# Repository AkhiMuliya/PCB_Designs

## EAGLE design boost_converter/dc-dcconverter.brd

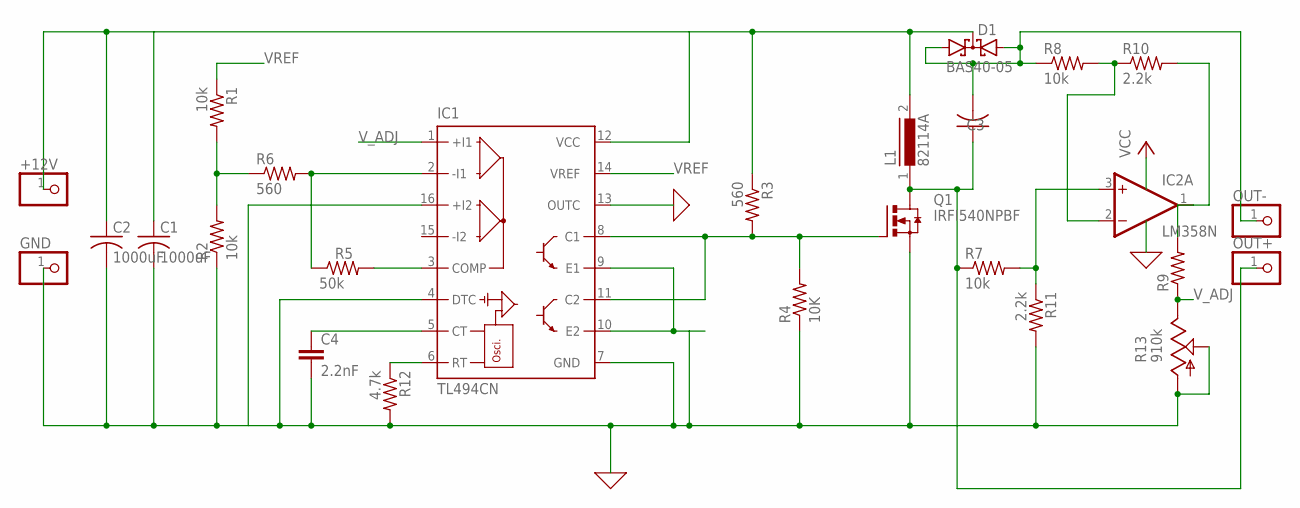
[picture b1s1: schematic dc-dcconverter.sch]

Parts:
+12V: PINHD-1X1; 1X01
C1, C2: 1000uF; C025-024X044
C3: C-US025-024X044; C025-024X044
C4: 2.2nF; C2.5-3
D1: BAS40-05; SOT23
GND: PINHD-1X1; 1X01
IC1: TL494CN; DIL16
IC2: LM358N; DIL08
L1: 82114A
OUT+: PINHD-1X1; 1X01
OUT-: PINHD-1X1; 1X01
Q1: IRFI540NPBF; TO220BH
R1, R2, R7, R8: 10k; 0204/5
R3, R6: 560; 0204/5
R4: 10K; 0204/5
R5: 50k; 0204/5
R9: R-US_0204/5; 0204/5
R10, R11: 2.2k; 0204/5
R12: 4.7k; 0204/5
R13: 910k; CA6H

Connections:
0: IC1.13 (OUTC)
GND: C1.2, C2.2, C4.2, GND.1, IC1.4 (DTC), IC1.7 (GND), IC1.9 (E1), IC1.10 (E2), IC1.16 (+I2), Q1.S, R2.1, R4.1, R11.2, R12.2, R13.A, R13.S
unnamed: IC1.2 (-I1), R5.1, R6.2
unnamed: IC1.3 (COMP), R5.2
unnamed: IC1.6 (RT), R12.1
unnamed: C4.1, IC1.5 (CT)
unnamed: IC1.8 (C1), IC1.11 (C2), Q1.G, R3.2, R4.2
unnamed: IC2.2 (-IN), R8.2, R10.1
unnamed: C3.1, L1.1, OUT+.1, Q1.D, R7.1
unnamed: C3.2, D1.1 (A1), D1.2 (A2), OUT-.1, R8.1
unnamed: IC2.1 (OUT), R9.2, R10.2
unnamed: R1.2, R2.2, R6.1
unnamed: IC2.3 (+IN), R7.2, R11.1
unnamed: +12V.1, C1.1, C2.1, D1.3 (C), IC1.12 (VCC), L1.2, R3.1
V+: IC2.8 (V+)
V-: IC2.4 (V-)
VREF: R1.1
V_ADJ: R9.1, R13.E

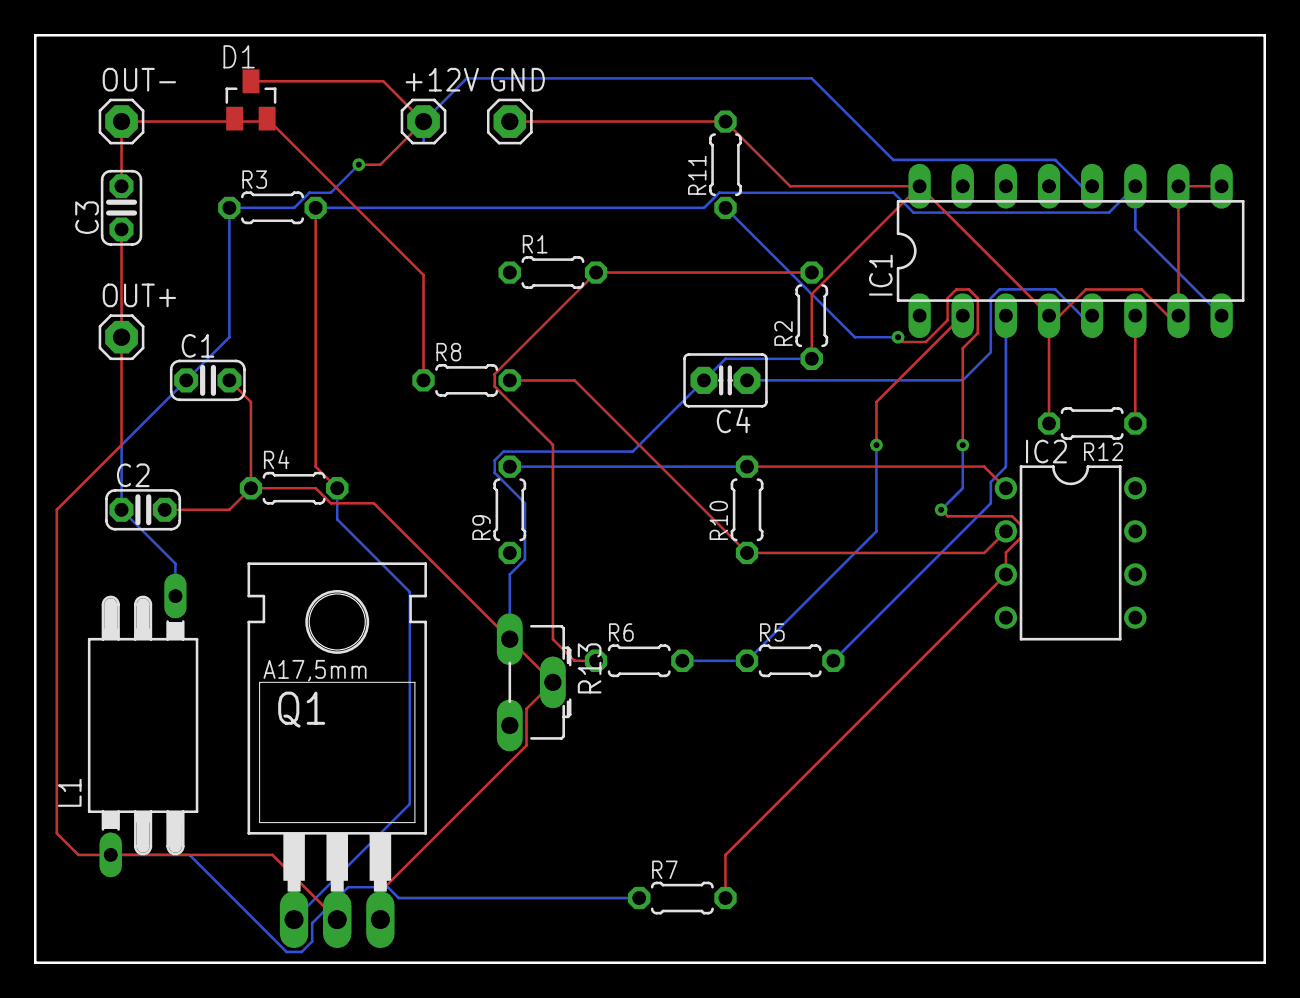
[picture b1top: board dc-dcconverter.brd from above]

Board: 2 copper layers, 72.4 x 54.6 mm, 26 parts (0 on the bottom side), 14 nets.

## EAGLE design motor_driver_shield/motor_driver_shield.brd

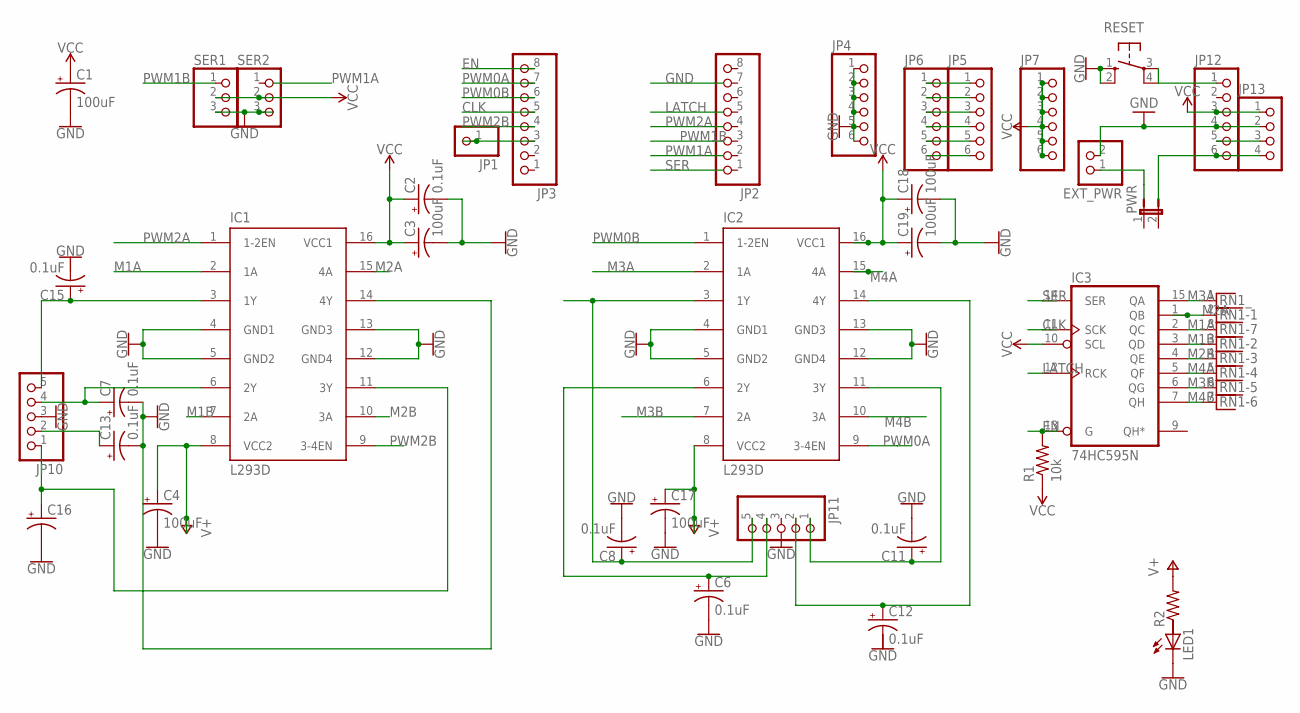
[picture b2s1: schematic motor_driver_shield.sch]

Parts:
C1, C3, C4, C17, C18, C19: 100uF; B45181A
C2, C6, C7, C8, C11, C12, C13, C15: 0.1uF; B45181A
C16: CPOL-USB45181A; B45181A
EXT_PWR: PINHD-1X2; 1X02
IC1, IC2: L293D; DIL16
IC3: 74HC595N; DIL16
JP1: PINHD-1X1; 1X01
JP2, JP3: PINHD-1X8-3.5MM; 1X08-3.5MM
JP4, JP5, JP6, JP7, JP12: PINHD-1X6-3.5MM; 1X06-3.5MM
JP10, JP11: PINHD-1X5; 1X05
JP13: PINHD-1X4; 1X04
LED1: LED5MM
PWR: JP1E; JP1
R1: 10k; 0204V
R2: R-US_0204/2V; 0204V
RESET: 40-XX; B3F-40XX
RN1: RNX7; RN-8
SER1, SER2: PINHD-1X3; 1X03

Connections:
CLK: IC3.11 (SCK), JP3.5
EN: IC3.13 (G), JP3.8, R1.2
GND: C1.-, C2.-, C3.-, C4.-, C6.-, C7.-, C8.-, C11.-, C13.-, C16.-, C17.-, C18.-, C19.-, EXT_PWR.2, IC1.4 (GND1), IC1.5 (GND2), IC1.12 (GND4), IC1.13 (GND3), IC1.14 (4Y), IC2.4 (GND1), IC2.5 (GND2), IC2.12 (GND4), IC2.13 (GND3), IC3.8 (GND), JP4.1, JP4.2, JP4.3, JP4.4, JP4.5, JP4.6, JP10.3, JP12.4, JP13.2, LED1.K (C), RESET.1 (S), RESET.2 (S1), SER1.3, SER2.3
LATCH: IC3.12 (RCK)
M1A: IC1.2 (1A), IC3.2 (QC), RN1.8
M1B: IC1.7 (2A), IC3.3 (QD), RN1.3
M2A: IC1.15 (4A), IC3.1 (QB), RN1.2
M2B: IC1.10 (3A), IC3.4 (QE), RN1.4
M3A: IC2.2 (1A), IC3.15 (QA), RN1.1
M3B: IC2.7 (2A), IC3.6 (QG), RN1.6
M4A: IC2.15 (4A), IC3.5 (QF), RN1.5
M4B: IC2.10 (3A), IC3.7 (QH), RN1.7
unnamed: JP5.1, JP6.1
unnamed: JP5.2, JP6.2
unnamed: JP5.3, JP6.3
unnamed: JP5.4, JP6.4
unnamed: JP5.5, JP6.5
unnamed: JP1.1, JP3.3
unnamed: JP5.6, JP6.6
unnamed: C11.+, IC2.11 (3Y), JP11.1
unnamed: C6.+, IC2.6 (2Y), JP11.4
unnamed: C8.+, IC2.3 (1Y), JP11.5
unnamed: JP12.1, RESET.3, RESET.4 (P1)
unnamed: JP12.5, JP13.3
unnamed: JP12.6, JP13.4
unnamed: C15.+, IC1.3 (1Y), JP10.5
unnamed: C16.+, IC1.11 (3Y), JP10.1
unnamed: C7.+, IC1.6 (2Y), JP10.4
unnamed: C13.+, JP10.2
unnamed: C12.+, IC2.14 (4Y), JP11.2
PWM0A: IC2.9 (3-4EN), JP3.7
PWM0B: IC2.1 (1-2EN), JP3.6
PWM1B: SER1.1
PWM2A: IC1.1 (1-2EN)
PWM2B: IC1.9 (3-4EN), JP3.4
SER: IC3.14 (SER)
V+: C4.+, C17.+, IC1.8 (VCC2), IC2.8 (VCC2), R2.2
VCC: C1.+, C2.+, C3.+, C18.+, C19.+, IC1.16 (VCC1), IC2.16 (VCC1), IC3.10 (SCL), IC3.16 (VCC), JP7.1, JP7.2, JP7.3, JP7.4, JP7.5, JP7.6, JP12.3, JP13.1, R1.1, SER1.2, SER2.2

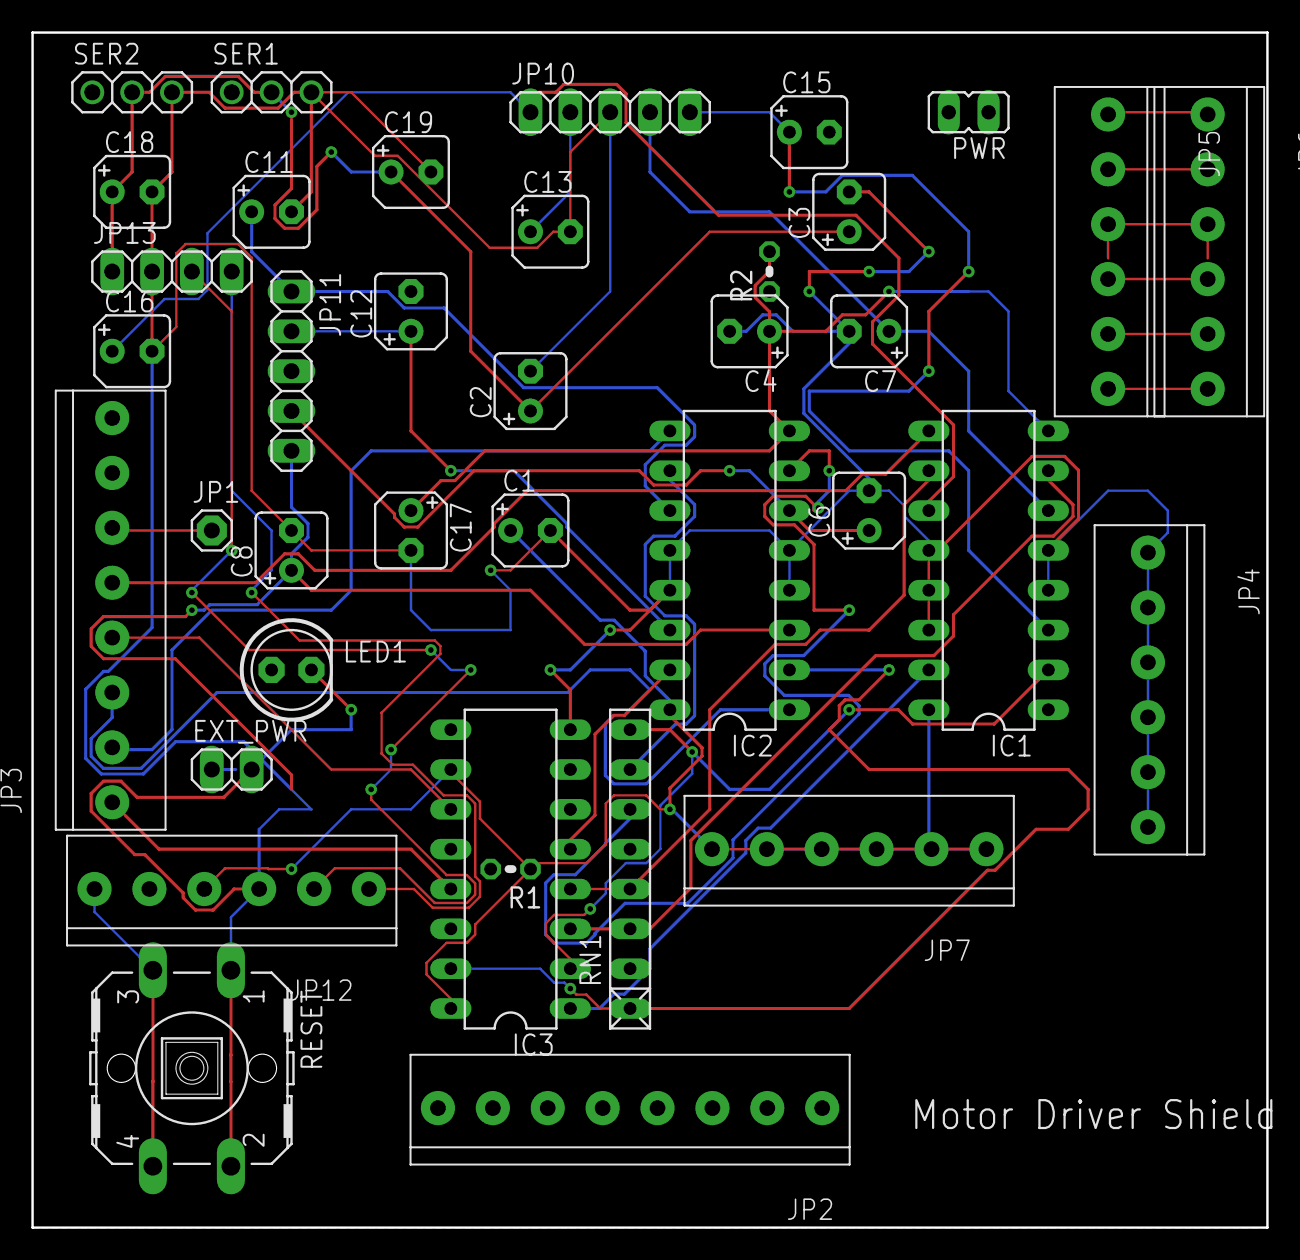
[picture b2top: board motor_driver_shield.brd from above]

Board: 2 copper layers, 78.7 x 76.2 mm, 38 parts (0 on the bottom side), 34 nets.

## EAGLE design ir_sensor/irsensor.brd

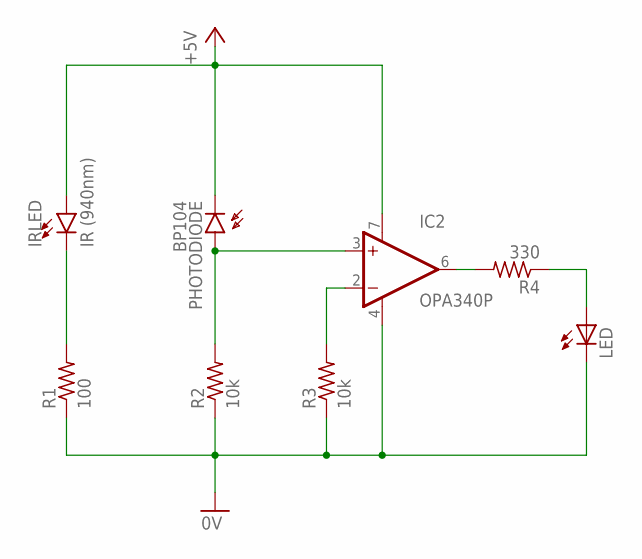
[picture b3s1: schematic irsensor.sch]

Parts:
IC2: OPA340P; DIL08
IRLED: IR (940nm); LED_5MM
LED: LED5MM
PHOTODIODE: BP104
R1: 100; 0204V
R2, R3: 10k; 0204V
R4: 330; 0204V

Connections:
0V: IC2.4 (V-), LED.K (C), R1.1, R2.1, R3.1
+5V: IC2.7 (V+), IRLED.A, PHOTODIODE.K (C)
unnamed: IRLED.K (C), R1.2
unnamed: IC2.3 (+IN), PHOTODIODE.A, R2.2
unnamed: IC2.6 (OUT), R4.2
unnamed: LED.A, R4.1
unnamed: IC2.2 (-IN), R3.2

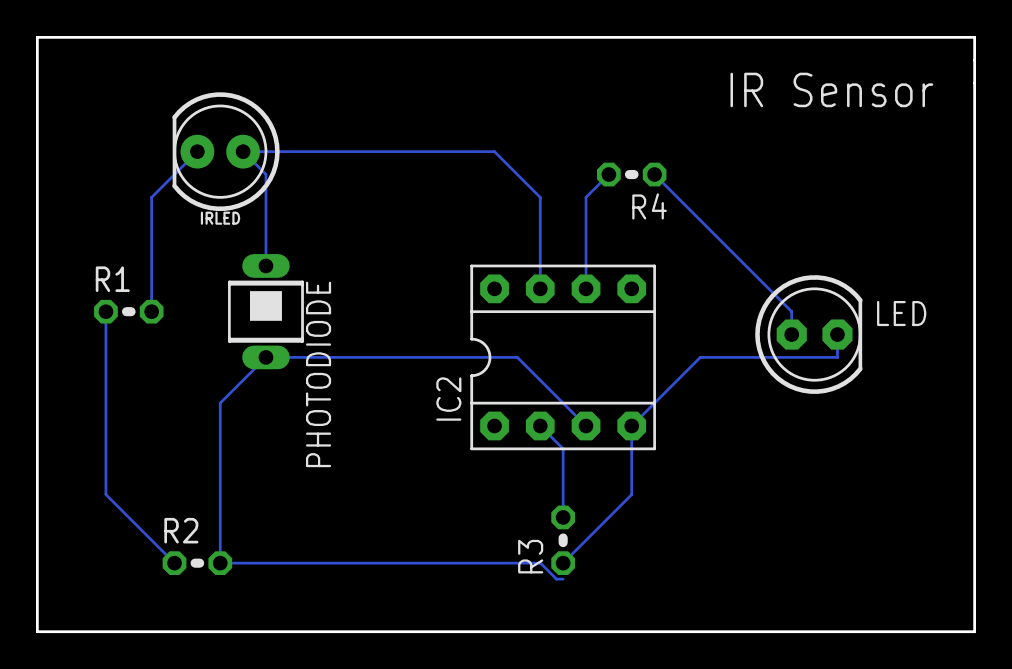
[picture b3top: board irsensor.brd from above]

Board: 2 copper layers, 52.1 x 33.0 mm, 8 parts (0 on the bottom side), 7 nets.

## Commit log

2024-03-12 Create brd&sch
2024-03-12 board&schematic
2024-03-12 Motor driver shield board and schematic
2024-06-10 Create boostconverter
2024-06-10 Create boost_converter
2024-06-10 Create schematic

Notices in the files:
parts and their libraries:
SparkFun-LED: Licensing: Creative Commons ShareAlike 4.0 International - https://creativecommons.org/licenses/by-sa/4.0
